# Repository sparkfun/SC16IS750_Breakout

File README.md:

SC16IS750 Breakout
=================

[  
*Breakout Board for SC16IS750 I2C/SPI-to-UART IC (BOB-09981)*](https://www.sparkfun.com/products/9981)

The SC16IS750 converts I<sup>2</sup>C or SPI serial signals to a single-channel, high-performance UART.

Repository Contents
-------------------
* **/Hardware** - All Eagle design files (.brd, .sch)

License Information
-------------------
The hardware is released under [Creative Commons Share-alike 3.0](http://creativecommons.org/licenses/by-sa/3.0/).

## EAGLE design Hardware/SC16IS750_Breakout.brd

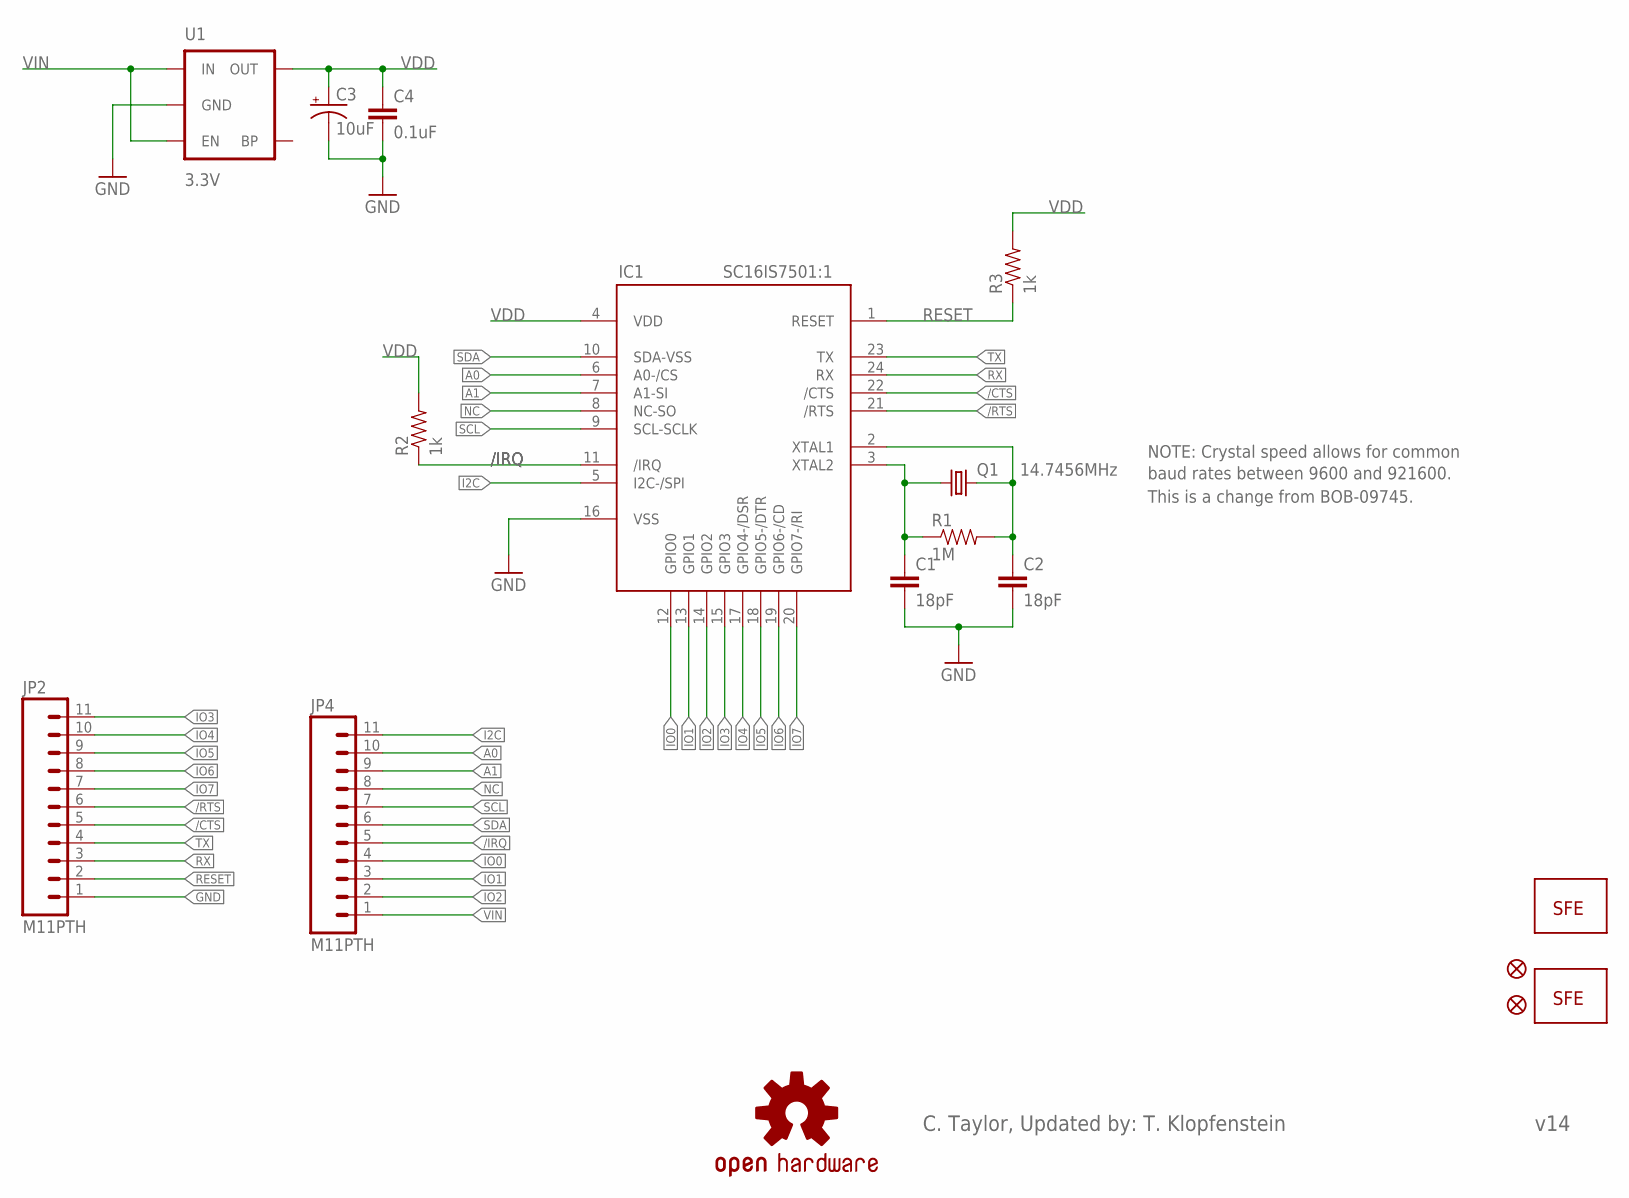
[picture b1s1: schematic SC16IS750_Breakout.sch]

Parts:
C1, C2: 18pF; 0603-CAP
C3: 10uF; EIA3216
C4: 0.1uF; 0603-CAP
IC1: SC16IS7501:1; QFN-24_1:1
JP1: LOGO-SFENEW; SFE-NEW-WEBLOGO
JP2, JP4: M11PTH; 1X11
JP3: LOGO-SFESK; SFE-LOGO-FLAME
JP5, JP6: FIDUCIAL1X2; FIDUCIAL-1X2
Q1: 14.7456MHz; CRYSTAL-SMD-5X3
R1: 1M; 0603-RES
R2, R3: 1k; 0603-RES
U1: 3.3V; SOT23-5
U$1: OSHW-LOGOS; OSHW-LOGO-S

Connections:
/CTS: IC1.22 (/CTS), JP2.5
/IRQ: IC1.11 (/IRQ), JP4.5, R2.1
/RTS: IC1.21 (/RTS), JP2.6
A0: IC1.6 (A0-/CS), JP4.10
A1: IC1.7 (A1-SI), JP4.9
GND: C1.2, C2.2, C3.C (-), C4.2, IC1.16 (VSS), JP2.1, U1.2 (GND)
I2C: IC1.5 (I2C-/SPI), JP4.11
IO0: IC1.12 (GPIO0), JP4.4
IO1: IC1.13 (GPIO1), JP4.3
IO2: IC1.14 (GPIO2), JP4.2
IO3: IC1.15 (GPIO3), JP2.11
IO4: IC1.17 (GPIO4-/DSR), JP2.10
IO5: IC1.18 (GPIO5-/DTR), JP2.9
IO6: IC1.19 (GPIO6-/CD), JP2.8
IO7: IC1.20 (GPIO7-/RI), JP2.7
unnamed: C1.1, IC1.3 (XTAL2), Q1.1, R1.1
unnamed: C2.1, IC1.2 (XTAL1), Q1.3 (2), R1.2
NC: IC1.8 (NC-SO), JP4.8
RESET: IC1.1 (RESET), JP2.2, R3.1
RX: IC1.24 (RX), JP2.3
SCL: IC1.9 (SCL-SCLK), JP4.7
SDA: IC1.10 (SDA-VSS), JP4.6
TX: IC1.23 (TX), JP2.4
VDD: C3.A (+), C4.1, IC1.4 (VDD), R2.2, R3.2, U1.5 (OUT)
VIN: JP4.1, U1.1 (IN), U1.3 (EN)

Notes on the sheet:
NOTE: Crystal speed allows for common
baud rates between 9600 and 921600.
This is a change from BOB-09745.
C. Taylor, Updated by: T. Klopfenstein
v14

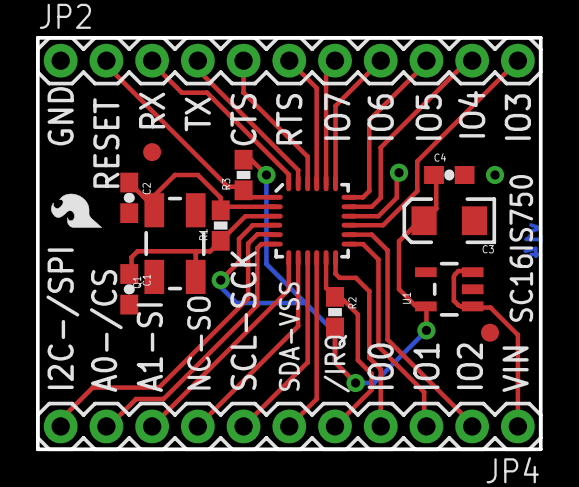
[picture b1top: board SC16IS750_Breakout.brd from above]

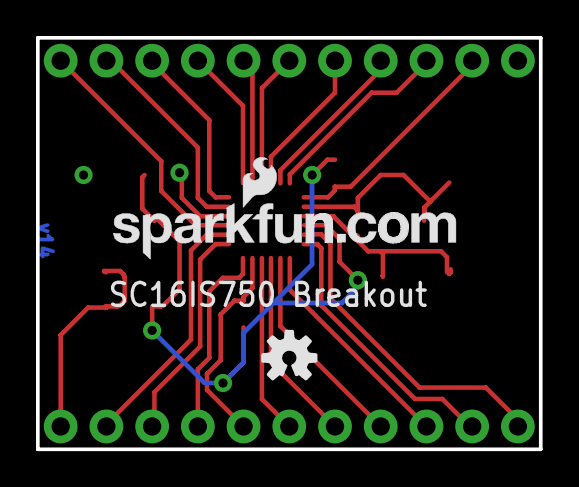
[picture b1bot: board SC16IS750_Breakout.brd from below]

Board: 2 copper layers, 27.9 x 22.9 mm, 18 parts (2 on the bottom side), 25 nets.

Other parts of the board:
U$2: CREATIVE_COMMONS

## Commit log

2013-05-08 Initial file commit and README update
2013-05-08 Added version number and description
2013-05-13 Fixed board files
2013-05-14 Fixed traces that were crooked
2013-05-14 Updated Package to "1:1" and rerouted traces directly away from IC
2013-08-19 Update README.md
    Fixing typos.
2015-01-19 Updating to current board files
2025-06-27 Update README.md
    Updating link

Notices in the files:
parts and their libraries:
SparkFun-Aesthetics: Licensing: CC v3.0 Share-Alike You are welcome to use this library for commercial purposes.
SparkFun-Aesthetics: Released under the Creative Commons Attribution Share-Alike 3.0 License
SparkFun-Aesthetics: Released under the Creative Commons
